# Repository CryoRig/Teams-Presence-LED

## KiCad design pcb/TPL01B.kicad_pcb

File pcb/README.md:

# TPL01B - Teams Presence Lamp

Open `TPL01B.kicad_pro` in KiCad 10, then open the schematic and PCB
from the project manager's tree. This is a routed prototype design (rev B), not
an approved manufacturing release. The firmware and hardware release gates below
must be completed before ordering an assembled production batch.

## Board

- 40 mm circular outline, two copper layers, nominal 0.8 mm FR4.
- Eight front-facing WS2812B-B-V6 5050 RGB LEDs at 45-degree intervals on a
	10.5 mm radius. The LED ring is centered on the board.
- ESP32-S3-MINI-1-N8 on the rear: 8 MB quad-SPI flash, no PSRAM, native USB,
	and an integrated Wi-Fi/Bluetooth antenna. A module avoids a custom crystal
	and RF matching circuit and is smaller than the WROOM alternative.
- Rear right-angle USB-C receptacle at the 6-o'clock edge; the cable exits
	sideways, parallel to the PCB, rather than above or below the lamp.
- Rear BOOT and RESET switches, accessible without relying on working firmware.
- SMD components throughout, except the explicitly approved USB shield anchors.
	Ground stitching and signal vias are ordinary PCB features, not THT parts.
- A rule area keeps tracks, vias, pads and pours off both faces at the module
	antenna. The round outline is kept, so FR4 remains under the antenna; this is
	an accepted limitation. RF performance has not been measured.

The 40 mm diameter is the selected prototype size, not a proof of the minimum
possible diameter. No mounting holes or enclosure mounting geometry are defined.
Provide mechanical cable strain relief; the thin PCB and USB socket must not
carry an unsupported cable load in the finished enclosure.

## Circuit

USB-C has independent 5.1 kohm CC pull-downs, both USB2 plug orientations wired,
USBLC6-2SC6 ESD protection, and 22 ohm series resistors near the ESP32 USB pins.
The shield connects directly to ground. There is no USB-to-UART converter or
USB Power Delivery controller.

A resettable fuse feeds the 5 V rail. An AP63203 buck regulator supplies 3.3 V;
a TPS22918 controlled-rise-time switch supplies the LEDs and their 5 V
AHCT level shifter. Per-LED decoupling and local bulk/IC capacitors are fitted;
C6 (100 nF) and C18 (22 uF, added in rev B) sit beside the module supply pin.
The switch defaults off through its enable pull-down. The fuse is fault
protection, not current negotiation or a guarantee of USB compliance.

| Function | ESP32-S3 GPIO |
| --- | --- |
| LED data | 2 |
| LED supply enable, active high | 4 |
| Native USB D- / D+ | 19 / 20 |
| BOOT, active low | 0 |
| Download-mode strap pull-down | 46 |
| UART test pads TX / RX | 43 / 44 |
| RESET | EN, not a GPIO |

Recovery procedure: hold BOOT, press and release RESET, then release BOOT.
This selects the chip's ROM downloader independently of the application. No
eFuse changes or alternative software recovery GPIO scheme are needed.

## Sourcing

All 47 populated parts have MPN/LCSC fields in the rev B schematic; the passive,
fuse and inductor identities and their review status come from
[ORDERING.md](ORDERING.md). Availability of the major parts below was
checked against the JLCPCB snapshot and live listings on 2026-11-09/10; the
snapshot omitted some parts that the live catalog carried. Stock is not reserved.

| References | Manufacturer Part | LCSC/JLCPCB |
| --- | --- | --- |
| U1 | ESP32-S3-MINI-1-N8 | C2913206 |
| J1 | TYPE-C-31-M-12 | C165948 |
| D2-D9 | WS2812B-B-V6 | C52941391 |
| U2 | AP63203WU-7 | C780769 |
| U3 | SN74AHCT1G125DBVR | C7484 |
| U4 | TPS22918DBVR | C131941 |
| D1 | USBLC6-2SC6 | C7519 |
| SW1, SW2 | B3U-1000P | C231329 |

`LampParts.kicad_sym`, `LampParts.pretty`, `LampParts.3dshapes` and the local
library tables supply the imported module and checked right-angle connector model.
The connector locator holes are NPTH; its soldered shield anchors are plated.
Module ground-pad numbering was checked against the shared MINI land pattern.
The connector uses the native KiCad HRO M12 land pattern and the matching supplier
STEP geometry in a project-local footprint. OpenCascade measurements of the
model's locator pegs and seating plane were compared with the manufacturer
drawing. Its 180-degree Z rotation and -1.05 mm model-Y offset align the pegs
with the footprint's locator centres at (+/-2.89, -2.60) mm. The 8.94 mm body
width and 3.25 mm model height agree with the drawing. The PCB's locator holes
are 0.65 mm; the four shield slots match the manufacturer's layout.

J1 is at (100, 116.9) mm on the rear, with its opening facing outwards and its
mouth slightly overhanging the circular edge. Native DRC checks the shield
tails against the opposite-face LED courtyards. Front, rear and side renders
were inspected after replacement. Physical assembly, plug and enclosure checks
are still required; a 3D rendering is not a mechanical qualification.

Smaller MINI-V6 and MINI-V3J LEDs were rejected as unqualified drop-in replacements:
their retrieved datasheets require a longer T1L than the installed XIAO driver's
375 ns default. The LEDs were WS2812B-B/W (C114586) until 2026-11-12, when
JLCPCB stopped offering that part for assembly. They are now WS2812B-B-V6
(C52941391): same maker, same 5050 land pattern and pin positions, and a data
timing table identical to the V5 one (T0H 220-380 ns, T1H/T0L/T1L 580-1000 ns,
reset above 280 us). The separate custom-board firmware keeps FastLED's V5
profile unchanged; the existing XIAO build keeps its original generic timing to
preserve the currently supported SK6812 hardware. Validate the actual LEDs and
waveform during prototype bring-up; do not silently substitute LED revisions.

## Firmware And Release Gates

**Do not flash the existing XIAO image and assume the lamp will work.** The
separate `tpl01_rev_b` PlatformIO target is configured for the 40 mm
ESP32-S3-MINI-1-N8 board (hardware variant 2), with GPIO4 LED-rail gating, a
provisional 250 mA FastLED LED budget and the WS2812B-V5 timing profile, which
also satisfies the selected WS2812B-B-V6 (C52941391). Startup does not transmit LED data until USB is
configured and the switched rail is enabled. The target compiles but has not
been validated on a fabricated board. The bridge updater still offers the
published XIAO image only for variant 1; initial 40 mm programming uses the
matching image and physical BOOT/RESET recovery. The existing XIAO target and
its 480 mA LED setting remain unchanged.

See [the prototype-order checklist](ORDERING.md) for whole-board USB power,
assembly sourcing, manufacturing and hardware-validation gates.

The current 480 mA FastLED limit covers LEDs only, not the ESP32 or regulator.
Before enabling LEDs, establish the total startup, configured, suspend and
future-radio power budgets, USB descriptor/current policy, and switch timing.
CC resistors alone do not authorize a 1.5 A or 3 A load. Verify input inrush,
rail droop, brownout behavior, LED data when unpowered, and regulator temperature.

Rev B routes both USB data lines on the rear only, without vias: from J1 through
the USBLC6 pads, the 22 ohm resistors and into U1, with D+ on the x=99.05 column
and D- on the x=100.95 column. Copper length between pad centres is 9.7 / 9.9 mm
(D+ / D-) for the B6/B7 plug orientation and 10.1 / 12.5 mm for A6/A7; the
2.4 mm difference is the bridge joining the two D- contacts around a D+ contact.
Impedance is deliberately not controlled: the tracks are 0.2 mm wide on 0.8 mm
two-layer FR4 and the front copper beneath them is crossed by LED supply tracks.
That is accepted for a 10 mm full-speed (12 Mbit/s) link; test both cable
orientations on the first boards.

The bootstrap capacitor C3 sits at U2 pins 5/6 beside the inductor's switch pad,
so BUCK_SW and BUCK_BST use no vias. C2 sits at U2 pins 3/4 with a direct ground
track and two ground vias outside the lands; the former via inside the pin 4
land is gone. The 3.3 V feedback runs from C4 to U2 pin 1 around C3. Ripple,
startup, load steps, temperature and EMI are unmeasured.

Initial assembly assumes hot air/reflow and a stencil, not a soldering iron
alone. Confirm the exact footprint drawings, connector/PCB thickness, solder
paste apertures, via-adjacent solder pads, moisture handling and reflow order.
Check every assembly rotation in the supplier preview before placing a PCBA
order. No manufacturing Gerbers/drills are approved here.

## Validation

On 2026-11-11, KiCad 10.0.8 native checks on rev B reported:

- Schematic ERC: zero reported violations.
- PCB DRC after zone refill: zero violations, zero unconnected items and zero
	schematic-parity issues, using the project's configured check set.
- Independent schematic-to-PCB audit: all 173 intended pin/net assignments match;
	51 physical footprints, two copper layers, 40 mm outline, eight equally spaced
	front LEDs, and rear controller/USB/recovery controls.
- `tools/rev_b.py --verify` with the former rev A reference: USB data copper
	via-free on the rear, no via centre in an SMD land, outline, antenna rule area
	and LED/J1/U1/switch placements identical to rev A. Two ground vias still
	overlap a land with their annular ring only (C8 pad 2 by 0.225 mm, C16 pad 2
	by 0.09 mm); they were not changed.
- Front/rear copper inspection outputs generated under ignored `outputs/`.

The fabrication floor is 0.15 mm track width with 0.15 mm default clearance,
0.20 mm power clearance and 0.50 mm copper-edge clearance. Wider power routes
use the Power netclass, with short pad escapes where necessary. Confirm all
limits with the selected fabrication/assembly service; DRC is not an electrical,
thermal, RF or manufacturability certification.

Hardware testing is **not run**: no prototype of this PCB has been fabricated.
The existing bench lamps have not been flashed or used as proof of this design.

Use the development helpers only with a dedicated Python virtual environment
that can import the matching KiCad `pcbnew` bindings. For a read-only audit:

```text
python pcb/tools/check_board.py --netlist pcb/outputs/rev-b/netlist.xml --routing --connector
python pcb/tools/rev_b.py --verify
```

Export that XML from the current schematic first; generated outputs are not
included in the repository. `--connector` checks the specific M12 footprint,
grounded shield slots, locator holes and STEP transform. `rev_b.py --verify`
checks the current board without a reference; supply `--reference <board>` to
also compare the outline, antenna keepout and fixed placements with an earlier
board. The former rev A snapshot is not included.
`rev_b.py --schematic` and `--board` are the one-time record of the rev A to
rev B changes and refuse to run twice. `set_part.py` changes the Value, MPN,
LCSC and Datasheet fields of existing parts in schematic and board. Other helper switches perform
development layout/route operations and can replace routing; do not run them on
an edited board as a routine validation step.

The JLCPCB placement file is not the native KiCad position file. JLCPCB places
the centre of its own library footprint and reads bottom-side angles mirrored,
so `jlc_placement.py <review folder> --fetch` (easyeda2kicad environment)
downloads those footprints and `--fit` (pcbnew environment) fits each one to
the board pads and writes `jlc-placement.csv`, which `export_jlc_review.ps1`
turns into the CPL. Neither step modifies the board.

Freerouting's Windows native CLI 2.5.0 failed with missing GraalVM serialization
metadata for `ComponentOutline`. Routing used the official 2.5.0 JAR and an
isolated Java 25 runtime instead, with verified download SHA-256 values. Native
KiCad DRC, not Freerouting's completion score, is the final connectivity check.

## Copilot Connection

The local connector uses KiCAD-MCP-Server v2.8.3, installed outside this repository
in the sibling `KiCAD-MCP-Server/2.8.3` directory. Its Python dependencies are
isolated in that installation's `.venv`. The computer-specific VS Code MCP
configuration is in `.vscode/mcp.json`, which the repository already ignores.

Enable the KiCad API under Preferences > Preferences > Plugins. For live PCB
editing, open the PCB from the project manager rather than launching a separate
PCB Editor process: separate processes competed for the default Windows API
endpoint during setup.

Before edits, use `open_project` with this project's absolute path and check
`get_backend_state`. Expect `backend: ipc`, `realtime: true`, and this board's
path. File-based schematic edits require saving and closing the schematic editor
first, then reopening it afterward; do not edit the same document simultaneously.

Keep schematic, PCB, project, custom library, and design-rule source files under
version control. Local state, lock files, backups, and the `outputs/` directory
are ignored. Generate manufacturing files only after circuit review and ERC/DRC.

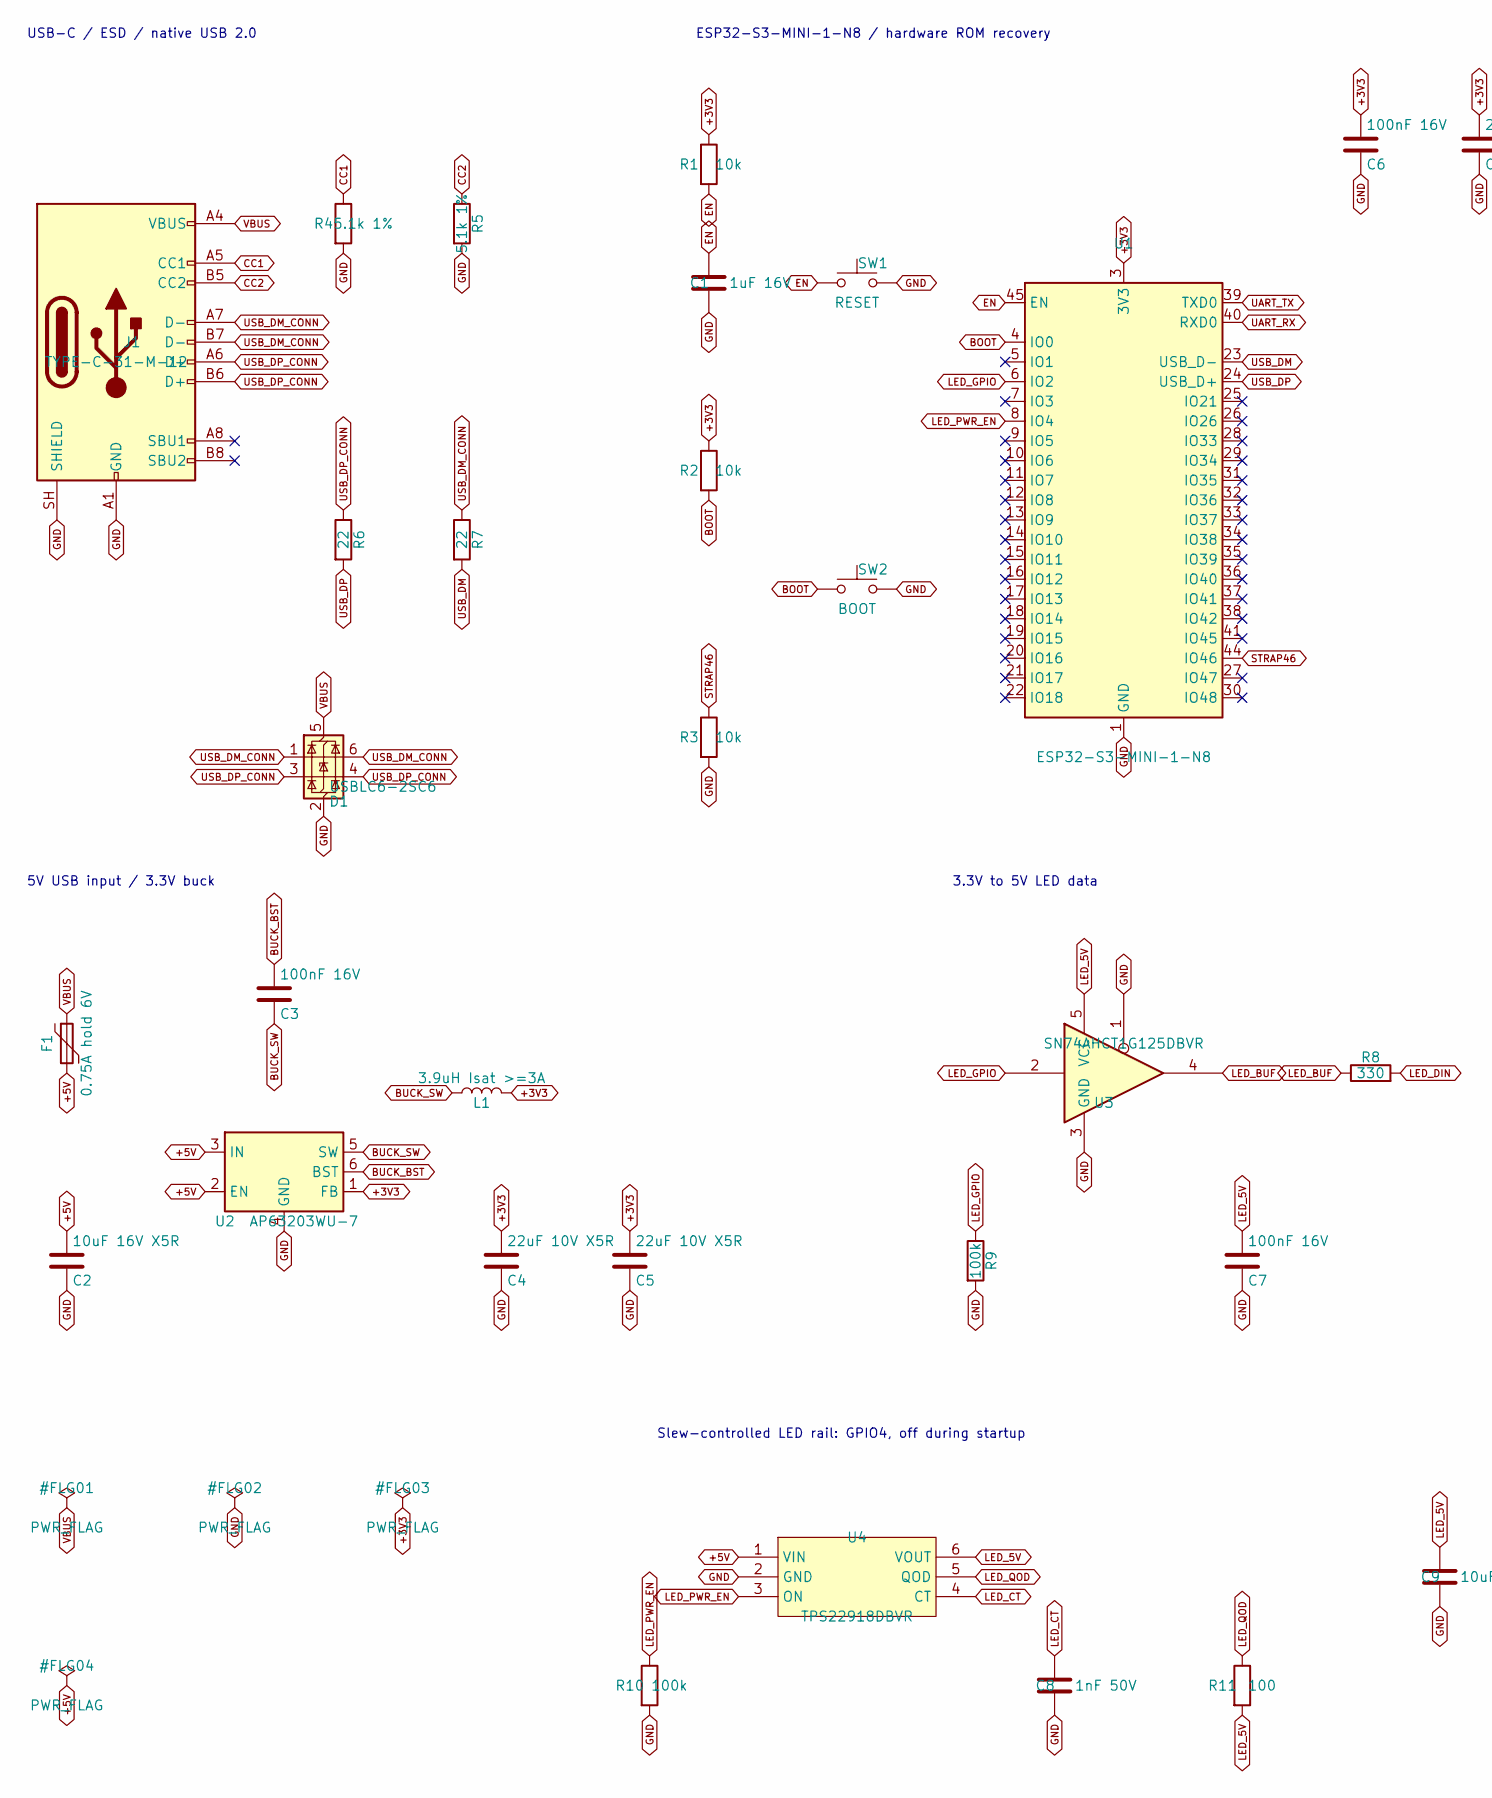
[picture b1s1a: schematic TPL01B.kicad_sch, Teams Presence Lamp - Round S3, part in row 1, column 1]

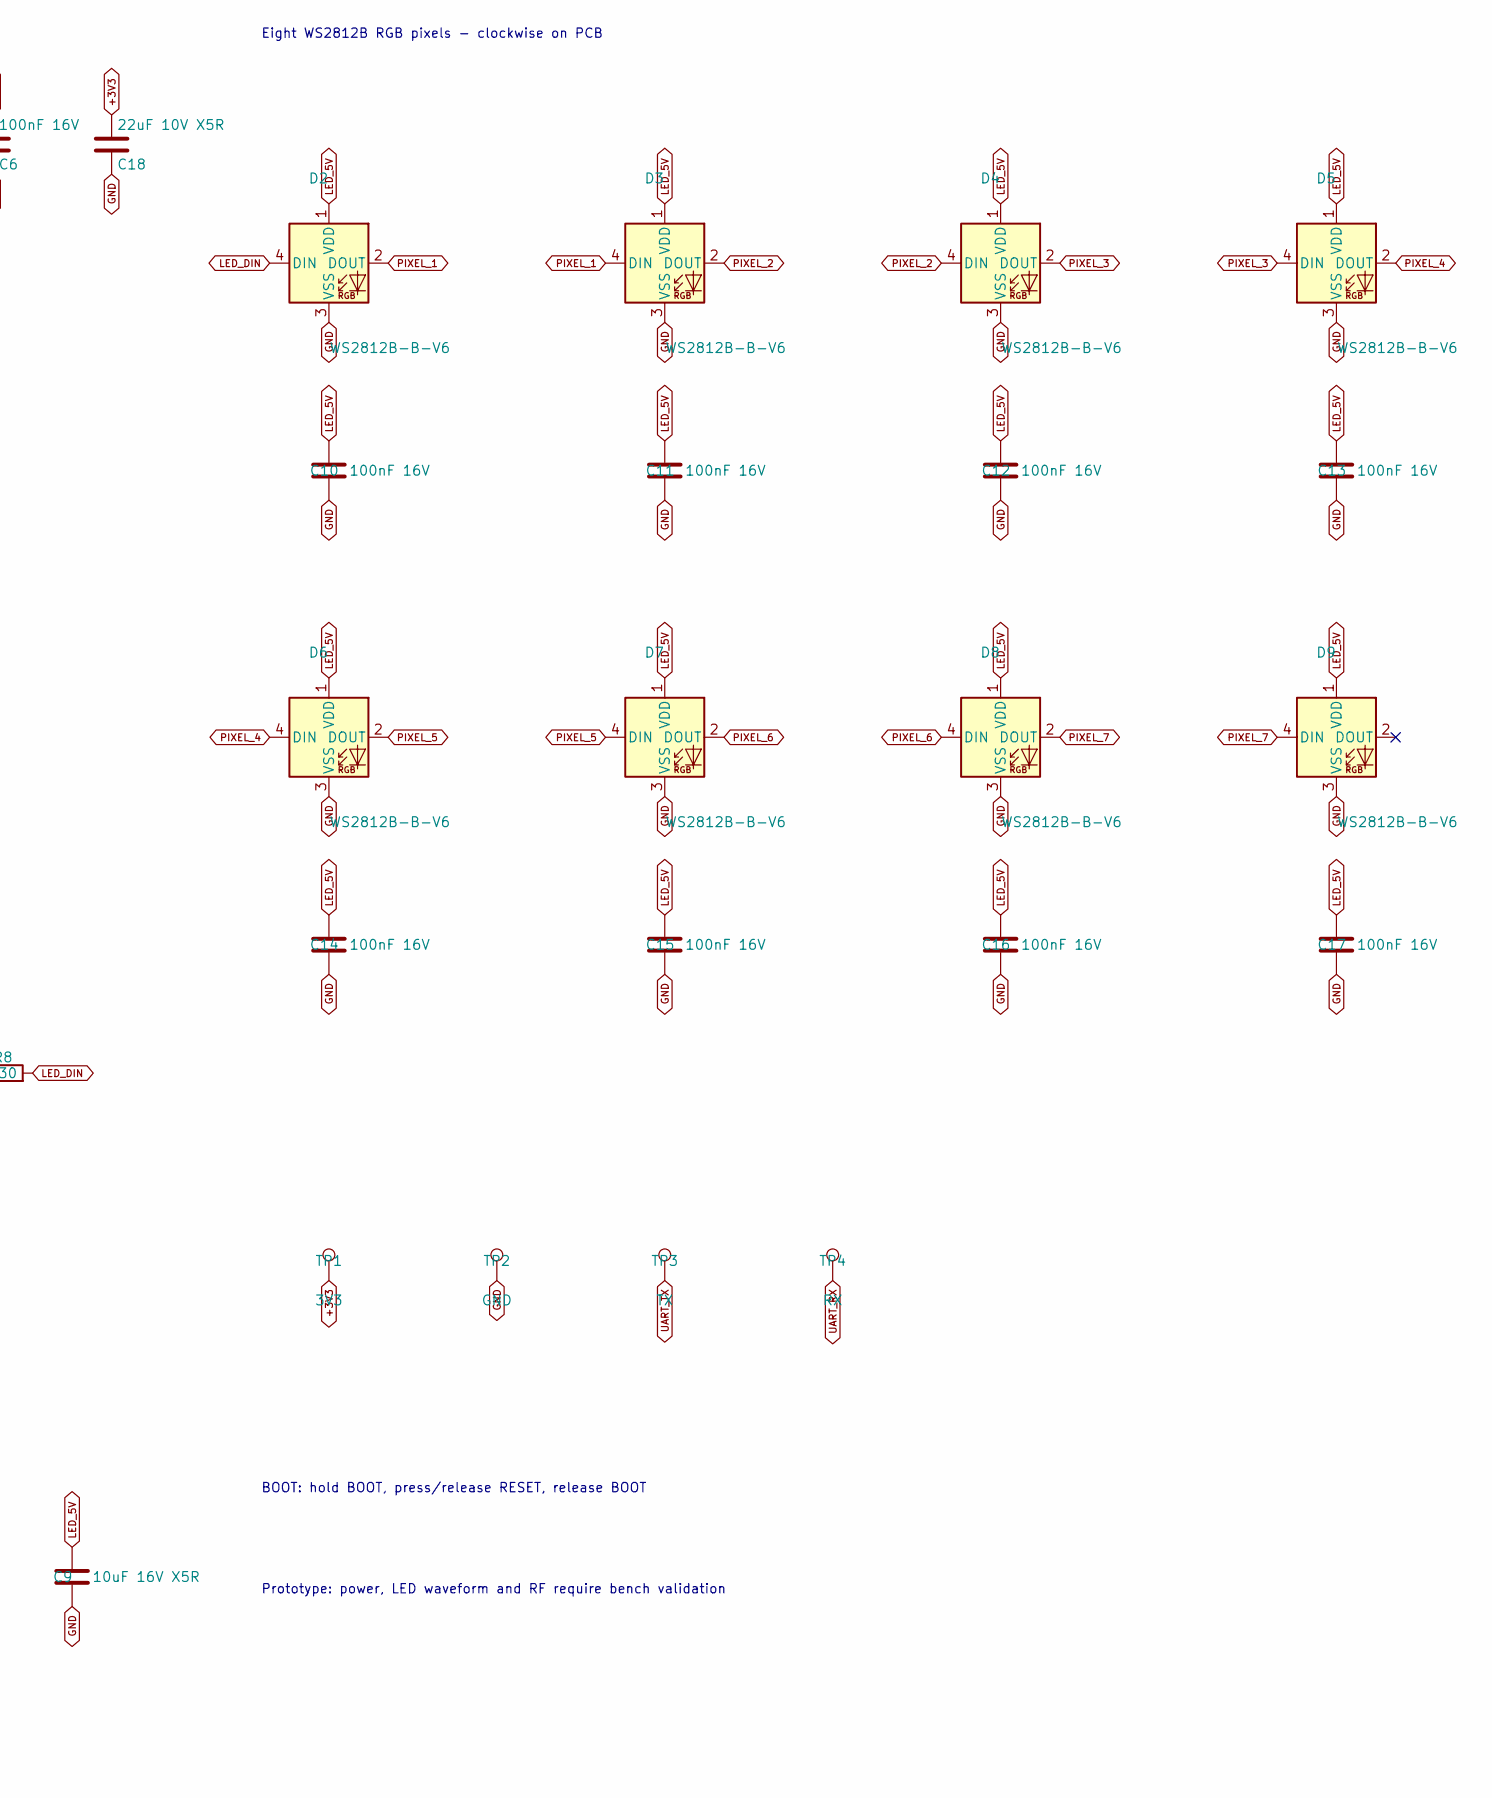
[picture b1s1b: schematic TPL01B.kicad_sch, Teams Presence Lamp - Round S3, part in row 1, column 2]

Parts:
C1: 1uF 16V; C_0603_1608Metric; MPN CL10B105KA8NNNC; LCSC C29936
C2, C9: 10uF 16V X5R; C_0805_2012Metric; MPN CL21A106KAYNNNE; LCSC C15850
C3, C6, C7, C10, C11, C12, C13, C14, C15, C16, C17: 100nF 16V; C_0603_1608Metric; MPN CC0603KRX7R9BB104; LCSC C14663
C4, C5, C18: 22uF 10V X5R; C_0805_2012Metric; MPN CL21A226MAYNNNE; LCSC C602037
C8: 1nF 50V; C_0603_1608Metric; MPN CC0603JRNPO9BN102; LCSC C106246
D1: USBLC6-2SC6; SOT-23-6; MPN USBLC6-2SC6; LCSC C7519
D2, D3, D4, D5, D6, D7, D8, D9: WS2812B-B-V6; LED_WS2812B_PLCC4_5.0x5.0mm_P3.2mm; MPN WS2812B-B-V6; LCSC C52941391
F1: 0.75A hold 6V; Fuse_1206_3216Metric; MPN SMD1206B075TF/16; LCSC C269118
J1: TYPE-C-31-M-12; USB_C_Receptacle_HRO_TYPE-C-31-M-12; MPN TYPE-C-31-M-12; LCSC C165948
L1: 3.9uH Isat >=3A; L_Bourns-SRN4018; MPN SWPA4030S3R9MT; LCSC C96899
R1, R2, R3: 10k; R_0603_1608Metric; MPN 0603WAF1002T5E; LCSC C25804
R4, R5: 5.1k 1%; R_0603_1608Metric; MPN 0603WAF5101T5E; LCSC C23186
R6, R7: 22; R_0603_1608Metric; MPN 0603WAF220JT5E; LCSC C23345
R8: 330; R_0603_1608Metric; MPN 0603WAF3300T5E; LCSC C23138
R9, R10: 100k; R_0603_1608Metric; MPN 0603WAF1003T5E; LCSC C25803
R11: 100; R_0603_1608Metric; MPN 0603WAF1000T5E; LCSC C22775
SW1: RESET; SW_SPST_B3U-1000P; MPN B3U-1000P; LCSC C231329
SW2: BOOT; SW_SPST_B3U-1000P; MPN B3U-1000P; LCSC C231329
TP1: 3V3; TestPoint_Pad_D1.0mm
TP2: GND; TestPoint_Pad_D1.0mm
TP3: TX; TestPoint_Pad_D1.0mm
TP4: RX; TestPoint_Pad_D1.0mm
U1: ESP32-S3-MINI-1-N8; BULETM-SMD_ESP32-S3-MINI-1-N8; MPN ESP32-S3-MINI-1-N8; LCSC C2913206
U2: AP63203WU-7; TSOT-23-6; MPN AP63203WU-7; LCSC C780769
U3: SN74AHCT1G125DBVR; SOT-23-5; MPN SN74AHCT1G125DBVR; LCSC C7484
U4: TPS22918DBVR; SOT-23-6; MPN TPS22918DBVR; LCSC C131941

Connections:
+3V3: C4.1, C5.1, C6.1, C18.1, L1.2, R1.1, R2.1, TP1.1, U1.3 (3V3), U2.1 (FB)
+5V: C2.1, F1.2, U2.2 (EN), U2.3 (IN), U4.1 (VIN)
BOOT: R2.2, SW2.1, U1.4 (IO0)
BUCK_BST: C3.1, U2.6 (BST)
BUCK_SW: C3.2, L1.1, U2.5 (SW)
CC1: J1.A5 (CC1), R4.1
CC2: J1.B5 (CC2), R5.1
EN: C1.1, R1.2, SW1.1, U1.45 (EN)
GND: C1.2, C2.2, C4.2, C5.2, C6.2, C7.2, C8.2, C9.2, C10.2, C11.2, C12.2, C13.2, C14.2, C15.2, C16.2, C17.2, C18.2, D1.2 (GND), D2.3 (VSS), D3.3 (VSS), D4.3 (VSS), D5.3 (VSS), D6.3 (VSS), D7.3 (VSS), D8.3 (VSS), D9.3 (VSS), J1.A1 (GND), J1.A12 (GND), J1.B1 (GND), J1.B12 (GND), J1.SH (SHIELD), R3.2, R4.2, R5.2, R9.2, R10.2, SW1.2, SW2.2, TP2.1, U1.1 (GND), U1.2 (GND), U1.42 (GND), U1.43 (GND), U1.46 (GND), U1.47 (GND), U1.48 (GND), U1.49 (GND), U1.50 (GND), U1.51 (GND), U1.52 (GND), U1.53 (GND), U1.54 (GND), U1.55 (GND), U1.56 (GND), U1.57 (GND), U1.58 (GND), U1.59 (GND), U1.60 (GND), U1.61 (GND), U1.62 (GND), U1.63 (GND), U1.64 (GND), U1.65 (GND), U2.4 (GND), U3.1, U3.3 (GND), U4.2 (GND)
LED_5V: C7.1, C9.1, C10.1, C11.1, C12.1, C13.1, C14.1, C15.1, C16.1, C17.1, D2.1 (VDD), D3.1 (VDD), D4.1 (VDD), D5.1 (VDD), D6.1 (VDD), D7.1 (VDD), D8.1 (VDD), D9.1 (VDD), R11.2, U3.5 (VCC), U4.6 (VOUT)
LED_BUF: R8.1, U3.4
LED_CT: C8.1, U4.4 (CT)
LED_DIN: D2.4 (DIN), R8.2
LED_GPIO: R9.1, U1.6 (IO2), U3.2
LED_PWR_EN: R10.1, U1.8 (IO4), U4.3 (ON)
LED_QOD: R11.1, U4.5 (QOD)
PIXEL_1: D2.2 (DOUT), D3.4 (DIN)
PIXEL_2: D3.2 (DOUT), D4.4 (DIN)
PIXEL_3: D4.2 (DOUT), D5.4 (DIN)
PIXEL_4: D5.2 (DOUT), D6.4 (DIN)
PIXEL_5: D6.2 (DOUT), D7.4 (DIN)
PIXEL_6: D7.2 (DOUT), D8.4 (DIN)
PIXEL_7: D8.2 (DOUT), D9.4 (DIN)
STRAP46: R3.1, U1.44 (IO46)
UART_RX: TP4.1, U1.40 (RXD0)
UART_TX: TP3.1, U1.39 (TXD0)
USB_DM: R7.2, U1.23 (USB_D-)
USB_DM_CONN: D1.1 (I/O1), D1.6 (I/O1), J1.A7 (D-), J1.B7 (D-), R7.1
USB_DP: R6.2, U1.24 (USB_D+)
USB_DP_CONN: D1.3 (I/O2), D1.4 (I/O2), J1.A6 (D+), J1.B6 (D+), R6.1
VBUS: D1.5 (VBUS), F1.1, J1.A4 (VBUS), J1.A9 (VBUS), J1.B4 (VBUS), J1.B9 (VBUS)

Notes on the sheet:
USB-C / ESD / native USB 2.0
ESP32-S3-MINI-1-N8 / hardware ROM recovery
Eight WS2812B RGB pixels - clockwise on PCB
5V USB input / 3.3V buck
3.3V to 5V LED data
Slew-controlled LED rail: GPIO4, off during startup
BOOT: hold BOOT, press/release RESET, release BOOT
Prototype: power, LED waveform and RF require bench validation

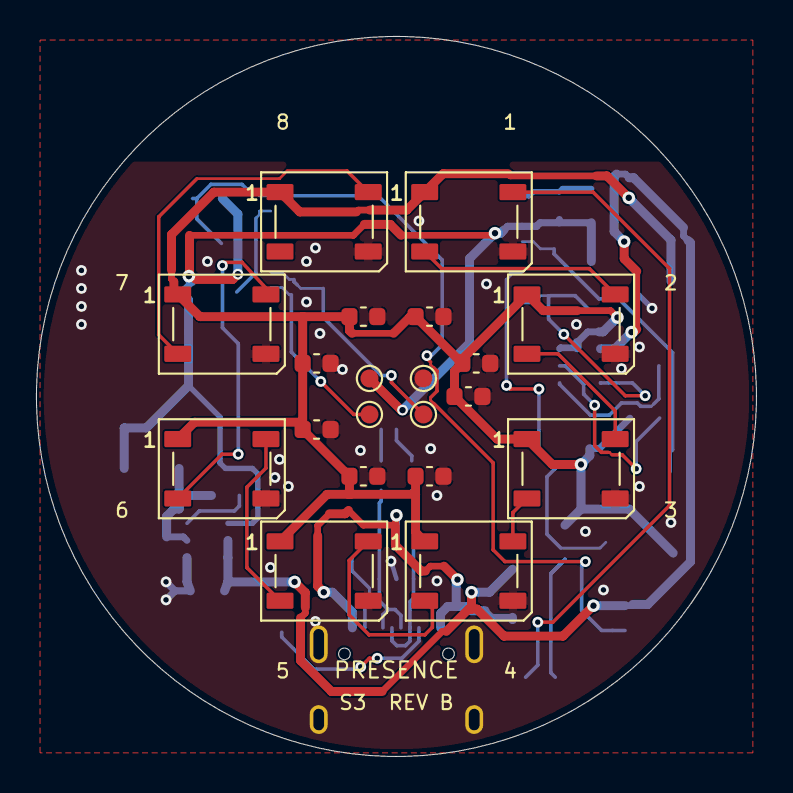
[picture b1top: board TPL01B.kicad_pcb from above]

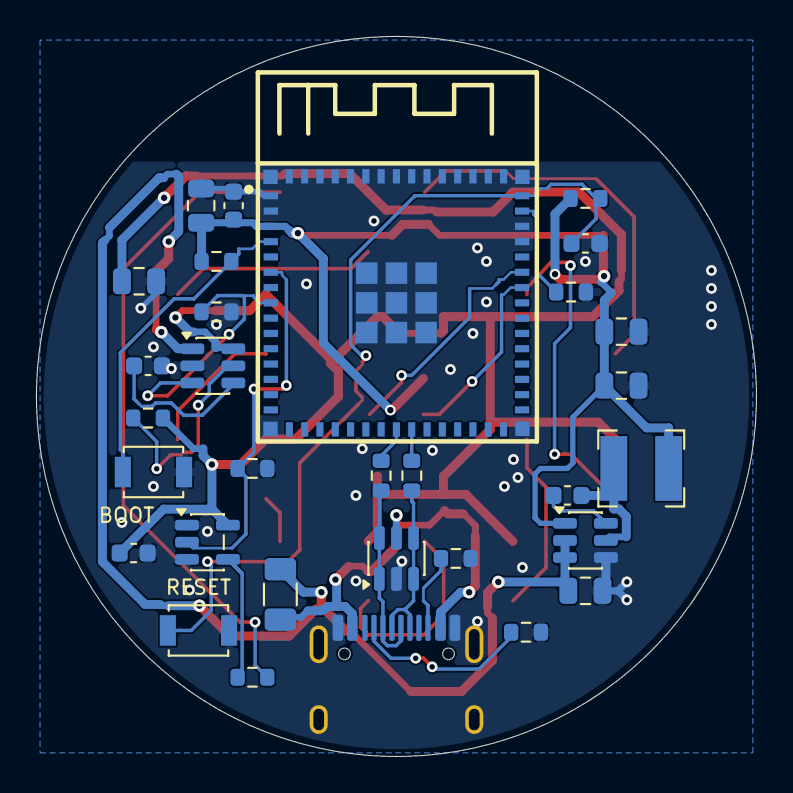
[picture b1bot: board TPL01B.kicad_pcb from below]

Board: 2 copper layers, 40.0 x 40.0 mm, 51 parts (31 on the bottom side), 31 nets.

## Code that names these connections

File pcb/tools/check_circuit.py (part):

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SCHEMATIC = ROOT / "TPL01B.kicad_sch"
CONNECTIONS = {
    "U1": {"1": "GND", "2": "GND", "3": "+3V3", "4": "BOOT",
           "6": "LED_GPIO", "8": "LED_PWR_EN", "23": "USB_DM", "24": "USB_DP",
           "39": "UART_TX", "40": "UART_RX", "44": "STRAP46", "45": "EN"},
    "R1": {"1": "+3V3", "2": "EN"},
    "R2": {"1": "+3V3", "2": "BOOT"},
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    "C5": {"1": "+3V3", "2": "GND"},
    "C6": {"1": "+3V3", "2": "GND"},
    "C18": {"1": "+3V3", "2": "GND"},
    "U3": {"1": "GND", "2": "LED_GPIO", "3": "GND", "4": "LED_BUF", "5": "LED_5V"},
    "R8": {"1": "LED_BUF", "2": "LED_DIN"},
    "R9": {"1": "LED_GPIO", "2": "GND"},
    "C7": {"1": "LED_5V", "2": "GND"},
    "U4": {"1": "+5V", "2": "GND", "3": "LED_PWR_EN", "4": "LED_CT",
           "5": "LED_QOD", "6": "LED_5V"},
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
